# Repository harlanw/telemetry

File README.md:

## Warning
This repository is extremely outdated. The firmware/software is many revisions behind and the hardware is outdated and has issues.

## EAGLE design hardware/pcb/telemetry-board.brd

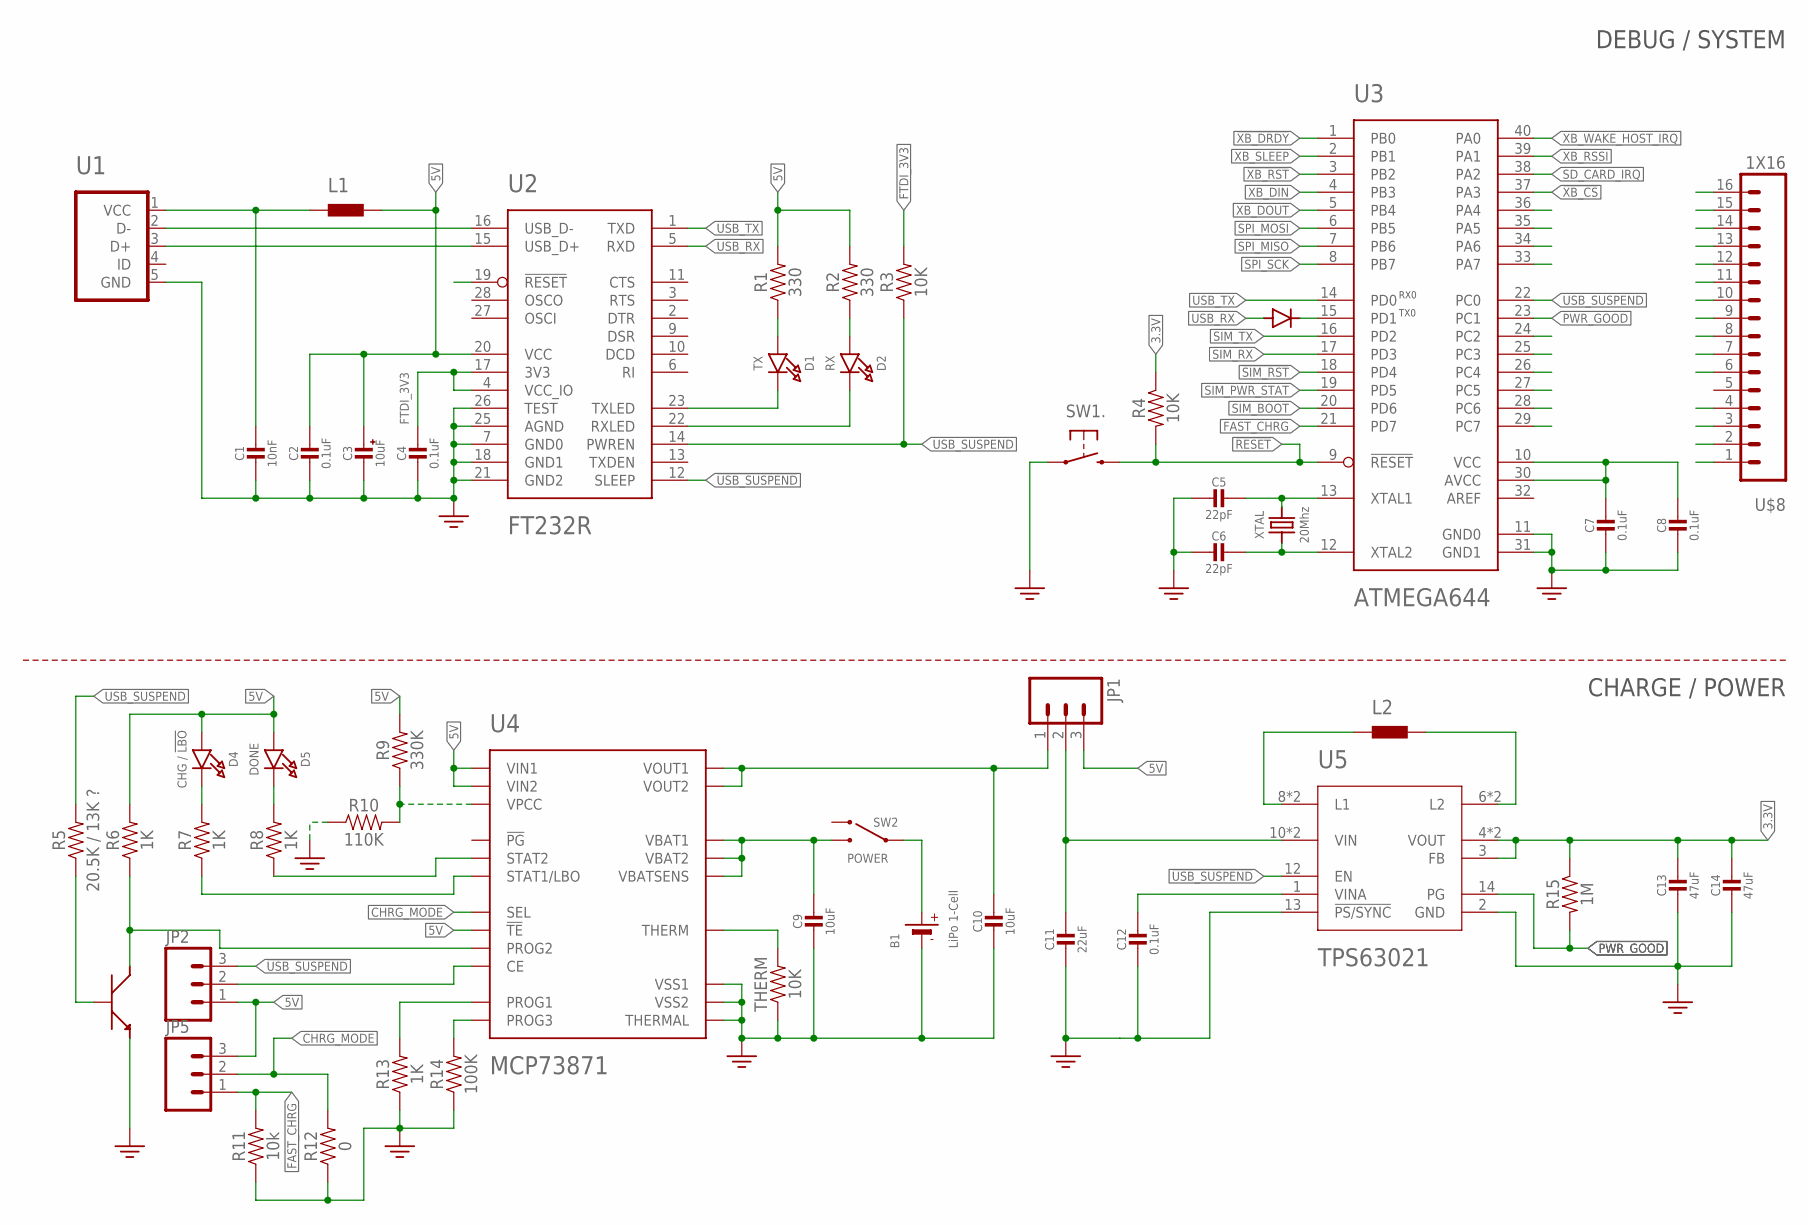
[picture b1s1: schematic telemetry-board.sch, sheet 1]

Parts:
B1: LiPo 1-Cell; JSTPH2
C1: 10nF; 0805
C2, C4, C7, C8, C12: 0.1uF; 0805
C3, C9, C10: 10uF; 0805
C5, C6: 22pF; 0805
C11: 22uF; 0805
C13, C14: 47uF; 0805
D1: TX; CHIPLED_0805_NOOUTLINE
D2: RX; CHIPLED_0805_NOOUTLINE
D3: DIODE; DB2J309
D4: CHG / !LBO; CHIPLED_0805_NOOUTLINE
D5: DONE; CHIPLED_0805_NOOUTLINE
JP1, JP2, JP5: M03PTH; 1X03
L1: INDUCTOR; 0805
L2: INDUCTOR-744062001; 2727
R1, R2: 330; 0805
R3, R4: 10K; 0805
R5: 20.5K / 13K ?; 0805
R6, R7, R8, R13: 1K; 0805
R9: 330K; 0805
R10: 110K; 0805
R11: 10k; 0805
R12: 0; 0805
R14: 100K; 0805
R15: 1M; 0805
SW1: SWITCH-B3U-1110-BOSS; SWITCH-TACT-B3U-1100P-B
SW2: POWER; 1101M2S4AQE2
THERM: 10K; 0805
U1: USB-RECEPTACLE; USB-MICRO-B
U2: FT232R; SSOP-28
U3: ATMEGA644; DIP-2X20
U4: MCP73871; QFN20_4MM
U5: TPS63021; VSON-14-4X3
U$2: TRANSISTOR; SOT-223
U$8: 1X16
XTAL: 20Mhz; ABM3

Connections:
3.3V: C7.1, C8.1, C13.1, C14.1, R4.1, R15.1, U3.10 (VCC), U3.30 (AVCC), U5.3 (FB), U5.4 (VOUT), U5.5 (VOUT), U$8.7; also elsewhere on the board
5V: C2.1, C3.1, D4.A, D5.A, JP1.3, JP2.1, JP5.3, L1.2, R1.2, R2.2, R6.2, R9.2, U2.20 (VCC), U4.P$9 (!TE), U4.P$18 (VIN1), U4.P$19 (VIN2)
!FT_RESET: U2.19 (!RESET)
!RESET: R4.2, SW1.2, U3.9 (!RESET); also elsewhere on the board
!SIM_RST: U3.18 (PD4); also elsewhere on the board
!USB_SUSPEND: JP2.3, U2.12 (SLEEP), U5.12 (EN)
!XB_CS: U3.37 (PA3); also elsewhere on the board
!XB_DRDY: U3.1 (PB0); also elsewhere on the board
!XB_RST: U3.3 (PB2); also elsewhere on the board
AREF: U3.32 (AREF)
BASE: R5.1, U$2.B
CE: JP2.2, U4.P$17 (CE)
CHRG_MODE: JP5.2, R12.2, U4.P$3 (SEL)
CTS: U2.11 (CTS)
DCD: U2.10 (DCD)
DSR: U2.9 (DSR)
DTR: U2.2 (DTR)
FAST_CHRG: JP5.1, R11.2, U3.21 (PD7), U$8.16
FROM_D3: D4.C, R7.2
FROM_D4: D5.C, R8.2
FTDI_3V3: C4.1, R3.2, U2.4 (VCC_IO), U2.17 (3V3)
GND: B1.1 (-), C1.2, C2.2, C3.2, C4.2, C5.1, C6.1, C7.2, C8.2, C9.2, C10.2, C11.2, C12.2, C13.2, C14.2, R10.1, R11.1, R12.1, R13.1, R14.1, SW1.1, THERM.1, U1.5 (GND), U2.7 (GND0), U2.18 (GND1), U2.21 (GND2), U2.25 (AGND), U2.26 (TEST), U3.11 (GND0), U3.31 (GND1), U4.P$10 (VSS1), U4.P$11 (VSS2), U4.P$21 (THERMAL), U5.2 (GND), U5.13 (!PS/SYNC), U$2.E, U$8.6; also elsewhere on the board
unnamed: C12.1, U5.1 (VINA)
OSCI: U2.27 (OSCI)
OSCO: U2.28 (OSCO)
PA4: U3.36 (PA4), U$8.1
PA5: U3.35 (PA5), U$8.2
PA6: U3.34 (PA6), U$8.3
PA7: U3.33 (PA7), U$8.4
PC2: U3.24 (PC2), U$8.13
PC3: U3.25 (PC3), U$8.12
PC4: U3.26 (PC4), U$8.11
PC5: U3.27 (PC5), U$8.10
PC6: U3.28 (PC6), U$8.9
PC7: U3.29 (PC7), U$8.8
PROG1: R13.2, U4.P$13 (PROG1)
PROG2: R6.1, U4.P$4 (PROG2), U$2.C0 (C), U$2.C1 (C)
PROG3: R14.2, U4.P$12 (PROG3)
PWR_GOOD: R15.2, U3.23 (PC1), U5.14 (PG), U$8.14
RI: U2.6 (RI)
RTS: U2.3 (RTS)
RXLED: D2.C, U2.22 (RXLED)
SD_CARD_IRQ: U3.38 (PA2); also elsewhere on the board
SIM_BOOT: U3.20 (PD6); also elsewhere on the board
SIM_PWR_STAT: U3.19 (PD5); also elsewhere on the board
SIM_RX: U3.17 (PD3); also elsewhere on the board
SIM_TX: U3.16 (PD2); also elsewhere on the board
SPI_MISO: U3.7 (PB6); also elsewhere on the board
SPI_MOSI: U3.6 (PB5); also elsewhere on the board
SPI_SCK: U3.8 (PB7); also elsewhere on the board
STAT1: R7.1, U4.P$8 (STAT1/LBO)
STAT2: R8.1, U4.P$7 (STAT2)
SYS_BAT: C10.1, JP1.1, U4.P$1 (VOUT1), U4.P$20 (VOUT2)
THERM: THERM.2, U4.P$5 (THERM)
TO_BAT: B1.2 (+), SW2.1P
TO_D1: D1.A, R1.1
TO_D2: D2.A, R2.1
TO_L1: L2.P$1 (1), U5.8 (L1), U5.9 (L1)
TO_L2: L2.P$2 (2), U5.6 (L2), U5.7 (L2)
TPS_VIN: C11.1, JP1.2, U5.10 (VIN), U5.11 (VIN)
TXDEN: U2.13 (TXDEN)
TXLED: D1.C, U2.23 (TXLED)
USB_5V: C1.1, L1.1, U1.1 (VCC)
USB_D+: U1.3 (D+), U2.15 (USB_D+)
USB_D-: U1.2 (D-), U2.16 (USB_D-)
USB_RX: D3.+, U2.5 (RXD)
USB_SUSPEND: R3.1, R5.2, U2.14 (PWREN), U3.22 (PC0), U$8.15
USB_TX: U2.1 (TXD), U3.14 (PD0)
VBAT: C9.1, SW2.2T, U4.P$14 (VBAT1), U4.P$15 (VBAT2), U4.P$16 (VBATSENS)
VPCC: R9.1, R10.2, U4.P$2 (VPCC)
XB_DIN: U3.4 (PB3); also elsewhere on the board
XB_DOUT: U3.5 (PB4); also elsewhere on the board
XB_RSSI: U3.39 (PA1); also elsewhere on the board
XB_SLEEP: U3.2 (PB1); also elsewhere on the board
XB_WAKE_HOST_IRQ: U3.40 (PA0); also elsewhere on the board
XTAL1: C5.2, U3.13 (XTAL1), XTAL.2
XTAL2: C6.2, U3.12 (XTAL2), XTAL.1
_USB_RX: D3.-, U3.15 (PD1)

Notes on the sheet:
DEBUG / SYSTEM
CHARGE / POWER
RX0
TX0

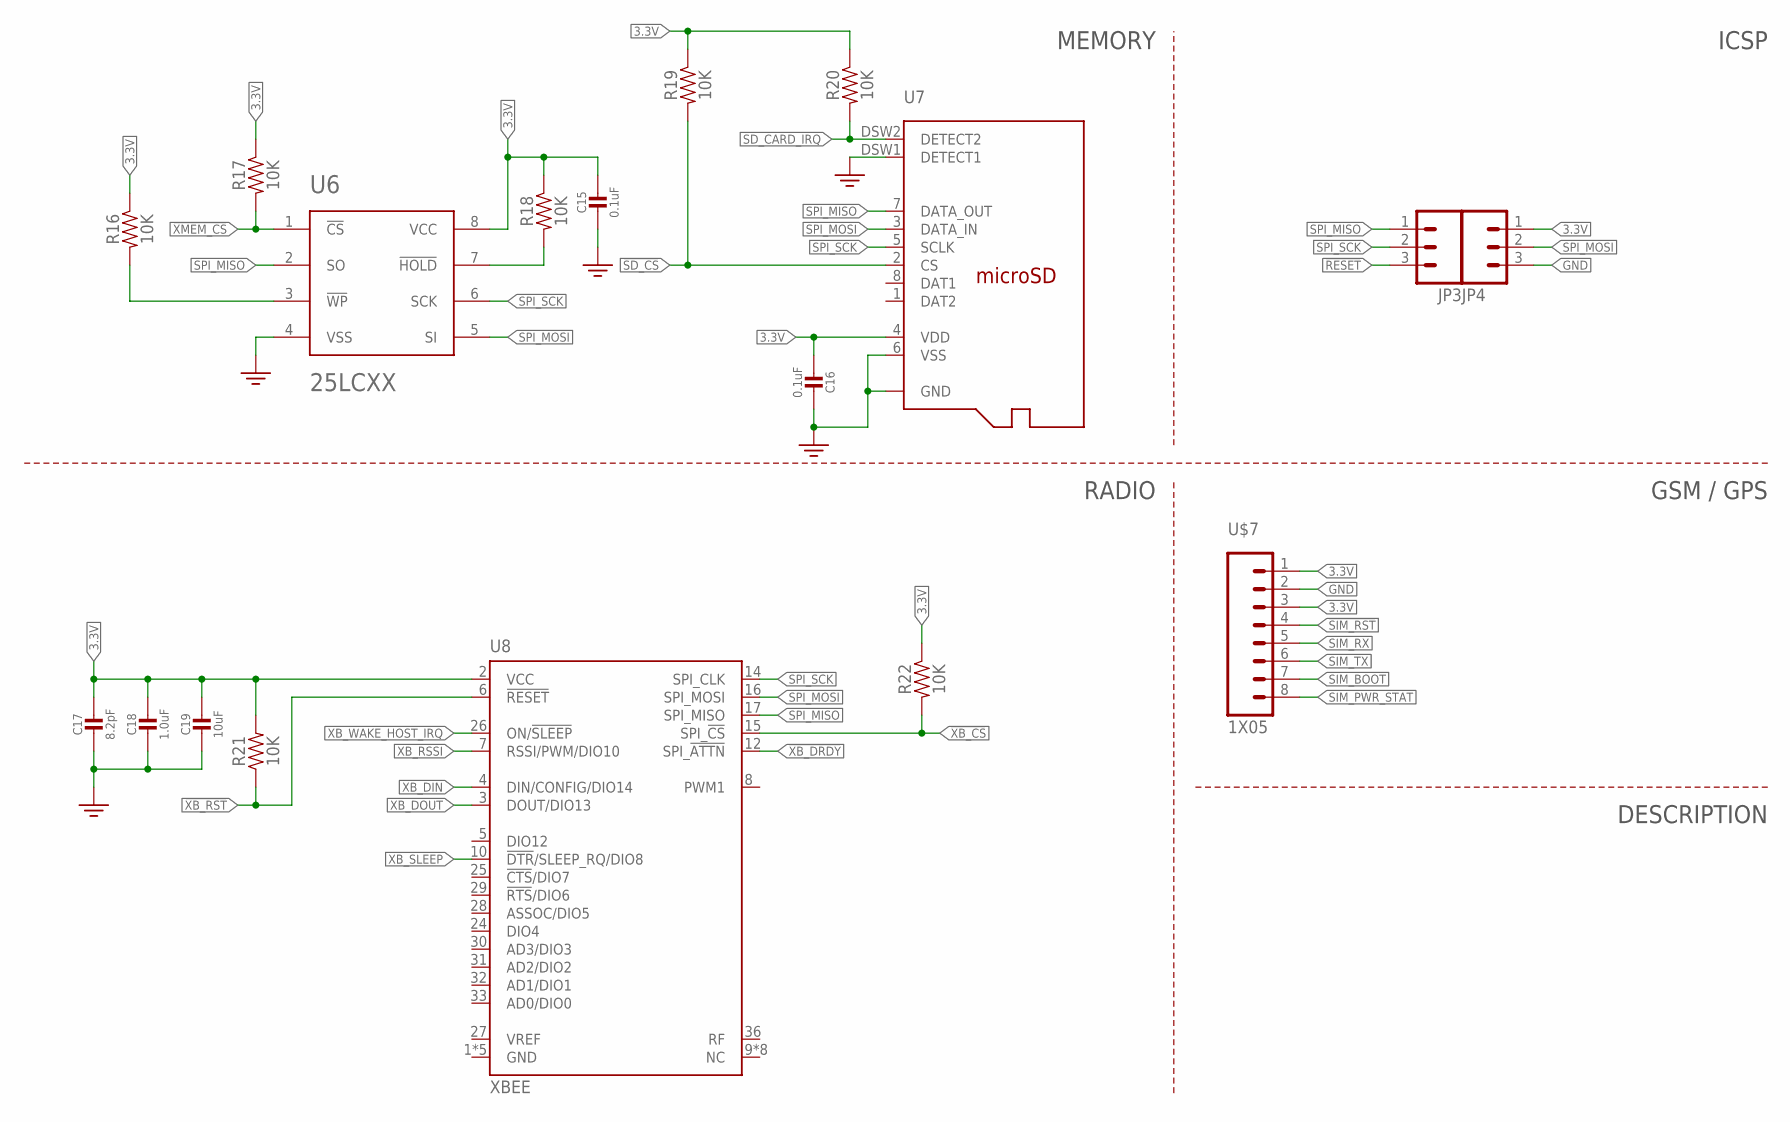
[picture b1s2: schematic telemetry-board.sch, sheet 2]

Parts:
C15, C16: 0.1uF; 0805
C17: 8.2pF; 0805
C18: 1.0uF; 0805
C19: 10uF; 0805
JP3, JP4: M031X03_NO_SILK; 1X03_NO_SILK
R16, R17, R18, R19, R20, R21, R22: 10K; 0805
U6: 25LCXX; DIP-2X4
U7: MICROSD
U8: XBEE; XBEE-S2C-SMNT
U$7: 1X05; DIP-1X5

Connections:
3.3V: C15.1, C16.1, C17.1, C18.1, C19.1, JP4.1, R16.1, R17.1, R18.1, R19.1, R20.1, R21.2, R22.1, U6.8 (VCC), U7.4 (VDD), U8.2 (VCC), U$7.1, U$7.3; also elsewhere on the board
!RESET: JP3.3; also elsewhere on the board
!SD_CS: R19.2, U7.2 (CS)
!SIM_RST: U$7.4; also elsewhere on the board
!XB_CS: R22.2, U8.15 (SPI_!CS); also elsewhere on the board
!XB_DRDY: U8.12 (SPI_!ATTN); also elsewhere on the board
!XB_RST: R21.1, U8.6 (!RESET); also elsewhere on the board
!XMEM_CS: R17.2, U6.1 (!CS)
!XMEM_HOLD: R18.2, U6.7 (!HOLD)
!XMEM_WP: R16.2, U6.3 (!WP)
GND: C15.2, C16.2, C17.2, C18.2, C19.2, JP4.3, U6.4 (VSS), U7.6 (VSS), U7.DSW1 (DETECT1), U7.GND1 (GND), U7.GND2 (GND), U7.GND3 (GND), U7.GND4 (GND), U7.GND5 (GND), U7.GND6 (GND), U7.GND7 (GND), U8.1 (GND), U8.11 (GND), U8.13 (GND), U8.22 (GND), U8.35 (GND), U$7.2; also elsewhere on the board
SD_CARD_IRQ: R20.2, U7.DSW2 (DETECT2); also elsewhere on the board
SIM_BOOT: U$7.7; also elsewhere on the board
SIM_PWR_STAT: U$7.8; also elsewhere on the board
SIM_RX: U$7.5; also elsewhere on the board
SIM_TX: U$7.6; also elsewhere on the board
SPI_MISO: JP3.1, U6.2 (SO), U7.7 (DATA_OUT), U8.17 (SPI_MISO); also elsewhere on the board
SPI_MOSI: JP4.2, U6.5 (SI), U7.3 (DATA_IN), U8.16 (SPI_MOSI); also elsewhere on the board
SPI_SCK: JP3.2, U6.6 (SCK), U7.5 (SCLK), U8.14 (SPI_CLK); also elsewhere on the board
XB_DIN: U8.4 (DIN/CONFIG/DIO14); also elsewhere on the board
XB_DOUT: U8.3 (DOUT/DIO13); also elsewhere on the board
XB_RSSI: U8.7 (RSSI/PWM/DIO10); also elsewhere on the board
XB_SLEEP: U8.10 (!DTR!/SLEEP_RQ/DIO8); also elsewhere on the board
XB_WAKE_HOST_IRQ: U8.26 (ON/!SLEEP); also elsewhere on the board

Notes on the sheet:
GSM / GPS
MEMORY
ICSP
DESCRIPTION
RADIO

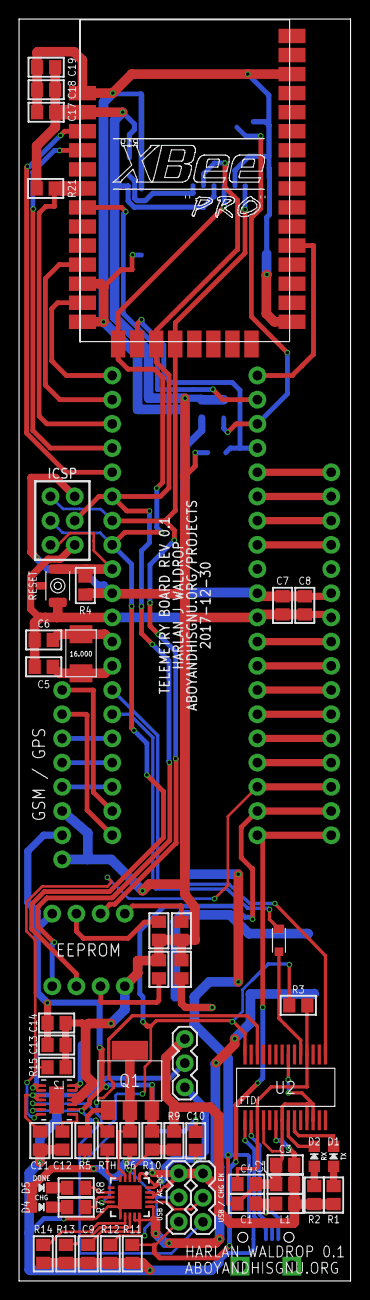
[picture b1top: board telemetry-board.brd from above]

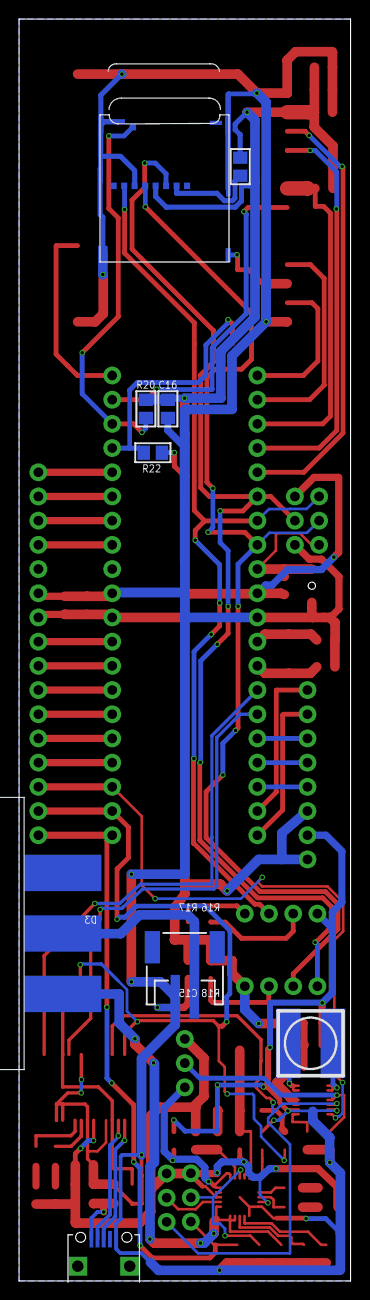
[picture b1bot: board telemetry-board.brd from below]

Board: 2 copper layers, 34.8 x 132.5 mm, 69 parts (9 on the bottom side), 71 nets.

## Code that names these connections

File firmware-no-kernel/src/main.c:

/**
 * @file main.c
 * @author Harlan J. Waldrop <waldroha@oregonstate.edu>
 * @date 2018-01-21
 *
 * @brief Post-kernel-initialization routines for kernel
 *
 * This file is responsible for adding and initializing any extra kernel tasks, as well as any other
 * routines required for system operation.
 *
 * @see ktask_add()
 * @see kinit()
 * @see kend()
 */
#include "kernel/sys/system.h"
#include "kernel/version.h"
#include "kernel/dev/modem.h"
#include "kernel/serial/spi.h"
#include "kernel/serial/uart.h"

#include <string.h>
#include <stdio.h>
#include <avr/io.h>
#include <util/delay.h>

#define XB_CS		3

#define XB_ATTN		0
#define XB_SLEEP	1
#define XB_RST		2
#define XB_DIN		3
#define XB_DOUT		4

uint8_t seek_frame = 0;
modem_t modem;

const char *
str = "{ \"error\": 0 }";

void
user_process(void)
{
	DDRA |= _BV(XB_CS) | _BV(0);
	PORTA = _BV(0);
	DDRB |= _BV(4) | _BV(3) | _BV(2) | _BV(1);
	PORTB |= _BV(XB_ATTN) | _BV(XB_RST);

	modem_create(&modem);
	modem.connect(NULL, 0);
	modem.write(str, strlen(str));

	while (modem.update() != -1)
	{
		if (modem.connection != MODEM_JOINED)
		{
			PANIC("FAILED TO CONNECT TO NETWORK");
		}
		else
		{
			modem.write(str, strlen(str));
		}

		_delay_ms(100);
	}
/*
	int ro = 1;
	while (1)
	{
		xbs2_poll();

		if ((PINB & _BV(XB_ATTN)))
		{
			/*
			if (ro)
			{
				uint8_t pkt[2] = {'H', 'V'};
				xbs2_at(pkt, NULL, 0);
				ro = 0;
				seek_frame = 1;
			}
		}
	}
	*/
}

/**
 * @brief System invocation routines
 *
 * @note On return immediately yields to kernel's end process, @kend()
 */
int
main(void)
{
	// TODO: Add kernel logging system
	kfinalize();
	user_process();

	return 0;
}

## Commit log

2018-01-16 basic serial over uart
2018-01-16 moved sys into kernel directory
2018-01-16 added hardware 0.0.1
2018-01-17 Began working on multi-threaded, pc-to-board interactive shell
2018-01-17 Removed duplicate, refactored threading code
2018-01-22 added preemptive task scheduler, began working on dynamic modules for tshl commands
2018-01-22 refactoring, added simavr target to Make
2018-02-12 old sources

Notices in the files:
parts and their libraries:
SparkFun-PowerSymbols: Licensing: Creative Commons ShareAlike 4.0 International - https://creativecommons.org/licenses/by-sa/4.0
